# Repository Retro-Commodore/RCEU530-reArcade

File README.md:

# RCEU530-reArcade
 new Arcade PCB with autofire

reArcade is an all microswitch drop-in replacement PCB for the Arcade joystick.  
Added is the possibility of an autofire using a 555 timer.  
Microswtich in firebutton - in case you don't want to modify the original pcb.  

In order to use autofire, a new cable is required which supplies 5v.

The long arm microswitch needs to be bent 90deg, 1.6-1.7cm from where it enters the house, then +1cm from there approx 80deg. You may need to test it by trial-and-error.

# BOM
4x Microswitches with regular size arm [eBay](https://www.ebay.com/itm/10-X-KW4-3Z-3-Hinge-Roller-Lever-SPDT-Momentary-Micro-Limit-Switch-3D-printer/122688679006).  
1x Microswitch with long arm [eBay](https://www.ebay.com/itm/5Pcs-AC250-125V-5A-3P-Momentary-36mm-Lever-Arm-Micro-Switch-Green-KW12-9S/233272820914).  
1x 1x7 pin male pinheader.  
  
**Optional Autofire**  
1x on/off switch  
1x SMD 0805 Resistor 33k  
1x SMD 0805 Resistor 4k7  
2x SMD 0805 Capacitor 10nF  
1x SMD 555 timer  
1x Joystick cable with 5v (min 7 wire cable, DB9 female, 1x7 pin female connector 2.54mm - or just get a finished extension cable on ebay).

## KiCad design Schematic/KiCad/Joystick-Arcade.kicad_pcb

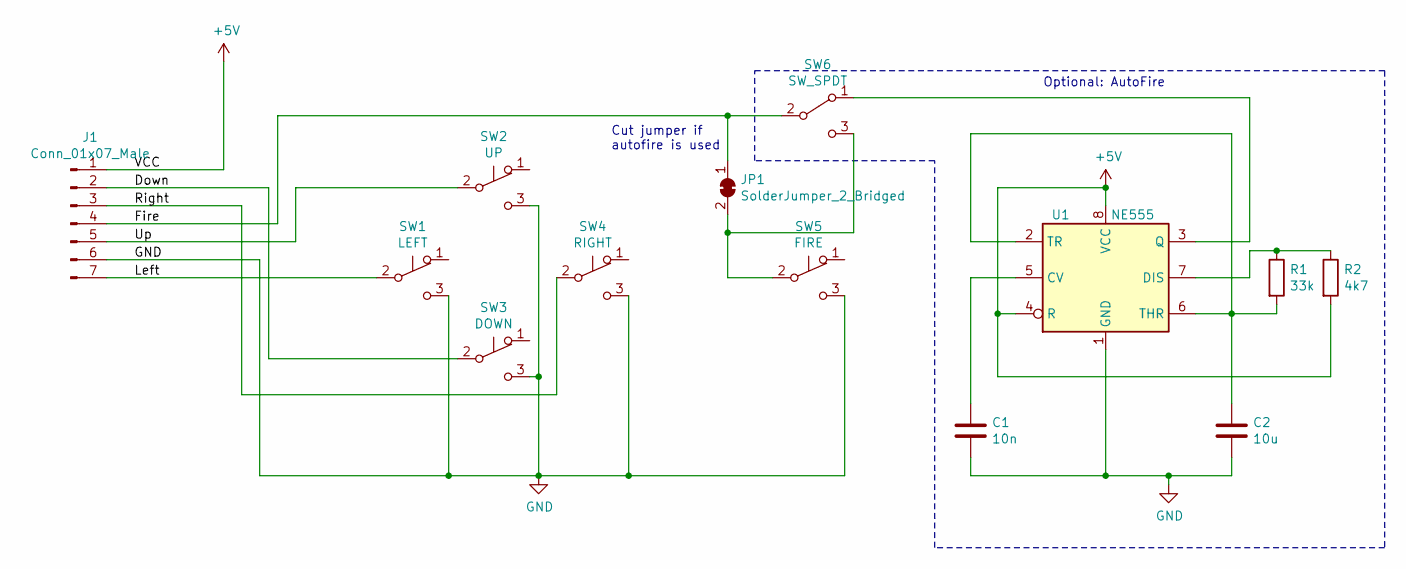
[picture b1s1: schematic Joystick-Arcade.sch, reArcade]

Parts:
C1: 10n; C_0805_2012Metric
C2: 10u; C_0805_2012Metric
J1: Conn_01x07_Male; PinHeader_1x07_P2.54mm_Vertical
JP1: SolderJumper_2_Bridged; SolderJumper-2_P1.3mm_Bridged_Pad1.0x1.5mm
R1: 33k; R_0805_2012Metric_Pad1.15x1.40mm_HandSolder
R2: 4k7; R_0805_2012Metric_Pad1.15x1.40mm_HandSolder
SW1: LEFT; Microswitch-no-nc-c-wire
SW2: UP; Microswitch-no-nc-c-wire
SW3: DOWN; Microswitch-no-nc-c-wire
SW4: RIGHT; Microswitch-no-nc-c-wire
SW5: FIRE; Microswitch-nc-no-c-pcb
SW6: SW_SPDT; SW_E-Switch_SS12D00G3_SPDT_Angled
U1: NE555; SO-8_5.3x6.2mm_Pitch1.27mm

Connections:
+5V: J1.1, R2.2, U1.4 (R), U1.8 (VCC)
/Down: J1.2, SW3.2 (B)
/Fire: J1.4, JP1.1 (A), SW6.2 (B)
/Left: J1.7, SW1.2 (B)
/Right: J1.3, SW4.2 (B)
/Up: J1.5, SW2.2 (B)
GND: C1.2, C2.2, J1.6, SW1.3 (C), SW2.3 (C), SW3.3 (C), SW4.3 (C), SW5.3 (C), U1.1 (GND)
unnamed: C1.1, U1.5 (CV)
unnamed: C2.1, R1.2, U1.2 (TR), U1.6 (THR)
unnamed: JP1.2 (B), SW5.2 (B), SW6.3 (C)
unnamed: R1.1, R2.1, U1.7 (DIS)
unnamed: SW6.1 (A), U1.3 (Q)

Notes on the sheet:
Optional: AutoFire
Cut jumper if autofire is used

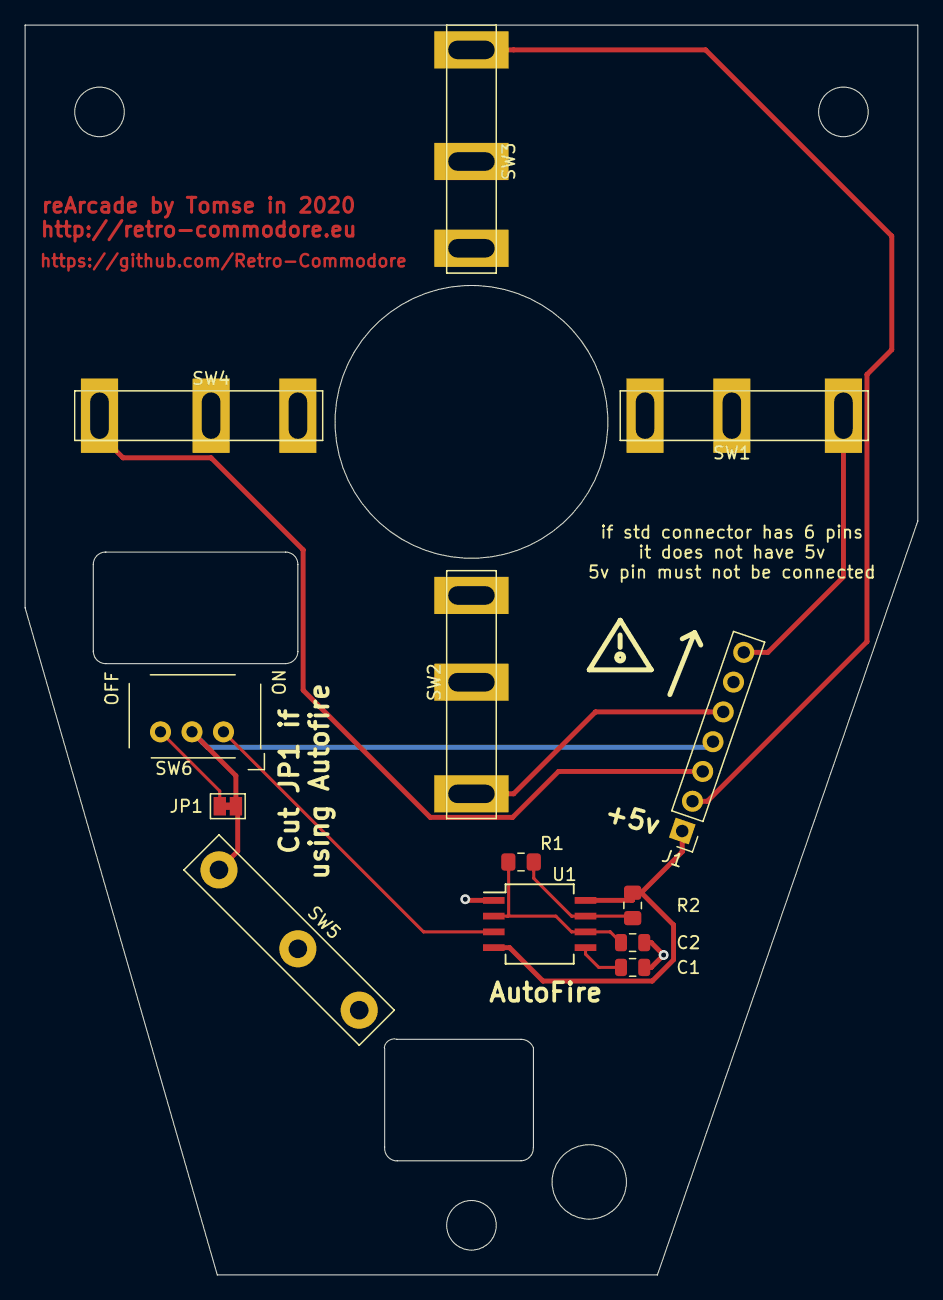
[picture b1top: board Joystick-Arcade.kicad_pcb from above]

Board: 2 copper layers, 72.0 x 100.8 mm, 13 parts (0 on the bottom side), 12 nets.

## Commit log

2020-08-23 initial release
    autofire not yet tested
